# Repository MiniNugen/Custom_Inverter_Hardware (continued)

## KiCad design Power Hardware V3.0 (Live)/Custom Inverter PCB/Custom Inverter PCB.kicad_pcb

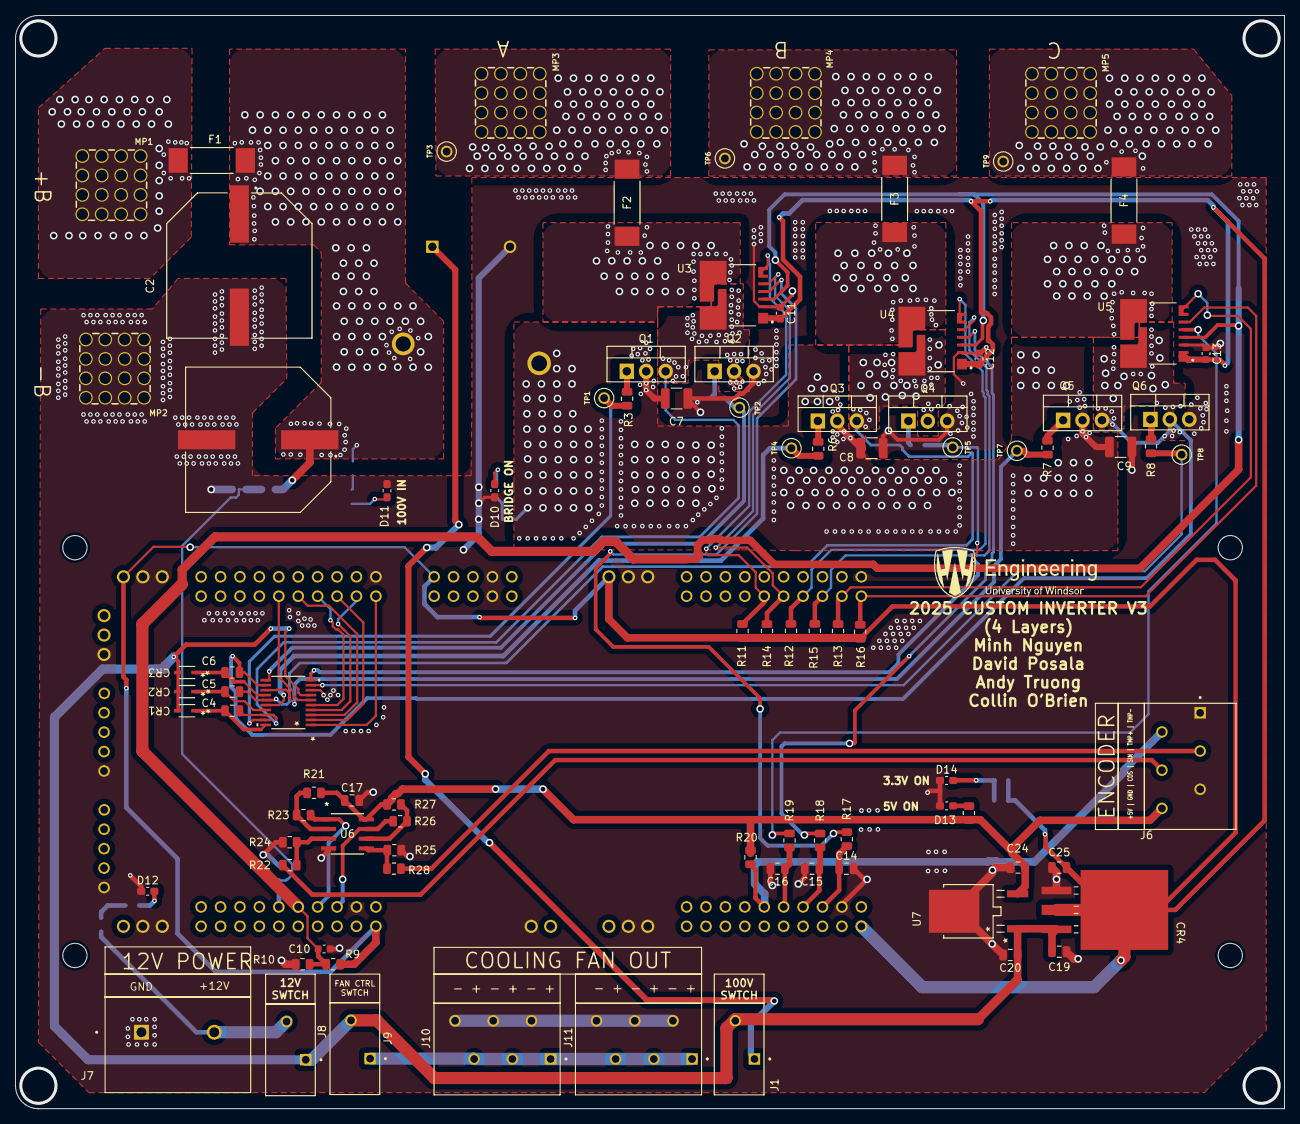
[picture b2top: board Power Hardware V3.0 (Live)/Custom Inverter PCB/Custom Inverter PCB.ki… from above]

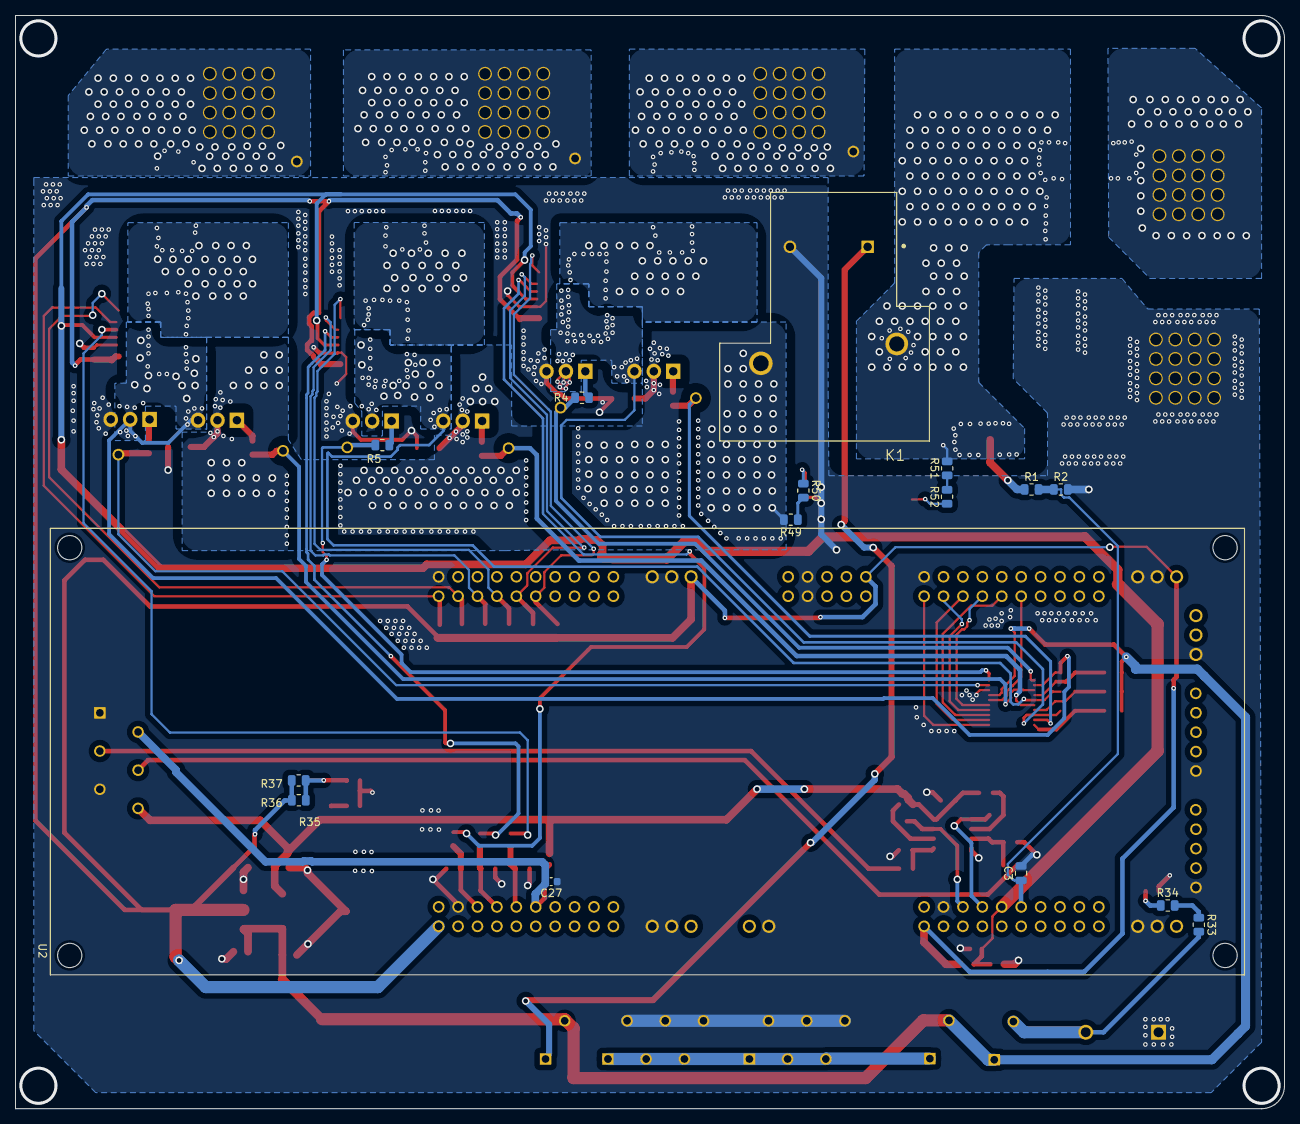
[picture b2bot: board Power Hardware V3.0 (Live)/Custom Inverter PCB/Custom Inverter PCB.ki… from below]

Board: 4 copper layers, 166.0 x 143.0 mm, 107 parts (16 on the bottom side), 71 nets.

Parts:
C1, C2: 330 µF; CAP_EEVFK2A331M
C3, C17, C24, C25: 0.1uF; C_0805_2012Metric
C4, C5, C6: 1uF; C_0805_2012Metric
C7, C8, C9: 1uF; C_1210_3225Metric
C10, C11, C12, C13, C27: 220nF; C_0603_1608Metric
C14, C15, C16: 47nF; C_0805_2012Metric
C19, C20: 0.33uF; C_0805_2012Metric
CR1, CR2, CR3: CR_SOD-323_MCC
CR4: LD1085D2M33R; D2PAK&slash_A_STM
D10: BRIDGE ON; C_0603_1608Metric_Pad1.08x0.95mm_HandSolder
D11: 100V IN; C_0603_1608Metric_Pad1.08x0.95mm_HandSolder
D12: 12V; C_0603_1608Metric_Pad1.08x0.95mm_HandSolder
D13: 5V; C_0603_1608Metric_Pad1.08x0.95mm_HandSolder
D14: 3.3V; C_0603_1608Metric_Pad1.08x0.95mm_HandSolder
F1: 100VDC 50A; FUSE_0463_LTF-M
F2, F3, F4: 250VAC 50A; FUSE_0463_LTF-M
J1, J8, J9: 1990009; PHOENIX_1990009
J6, J10, J11: 1990041; PHOENIX_1990041
J7: 1714971; PHOENIX_1714971
K1: 1-1393210-3; TE_1-1393210-3
MP1, MP2, MP3, MP4, MP5: 7461383; WP-SHFU_7461383
Q1, Q2, Q3, Q4, Q5, Q6: IRFB4115PBF; TO-220-3_Vertical
R1: 97.6K; R_0805_2012Metric
R2, R22, R23, R26, R28: 3K; R_0805_2012Metric
R3, R4, R5, R6, R7, R8: 15R; R_0805_2012Metric
R9, R10, R11, R12, R13, R14, R15, R16: 4.7K; R_0805_2012Metric
R17, R18, R19, R33, R34, R35, R36, R37: 220R; R_0805_2012Metric
R20: 5.36k; R_0805_2012Metric
R21, R24, R25, R27: 10k; R_0805_2012Metric
R49, R50, R51, R52: 2.7k; R_0805_2012Metric
TP1, TP2, TP3, TP4, TP5, TP6, TP7, TP8, TP9: 5002; KEYSTONE_5002
U1: DRV8300DIPWR; TSSOP_0DIPWR_TEX
U2: LAUNCHXL-F280049C; MODULE_LAUNCHXL-F280049C
U3, U4, U5: TLI4971A050T5E0001XUMA1; TLI4971A050T5UE0001XUMA1
U6: OP292GSZ-REEL; R_8_ADI
U7: L78M05CDT-TR; DPAK_STM-M

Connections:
+3.3VDC: C11.2, C12.2, C13.2, C25.1, CR4.2 (OUTPUT), CR4.4 (OUTPUT), R9.1, R11.1, R12.1, R13.1, R14.1, R15.1, R16.1, R36.2, R37.2, U2.J1_1 (+3.3V), U2.J5_41 (J5_+3.3V), U2.J11_10 (+3.3V), U2.JP4_1 (+3.3V), U2.JP6_1 (+3.3V), U3.1 (VDD), U4.1 (VDD), U5.1 (VDD)
+5V: C17.1, C24.1, J6.6, R20.2, R21.1, R27.1, R35.2, U6.8 (+V), U7.2 (OUTPUT)
+12V to relay: J7.2, J8.2, R33.2
+12VDC: C19.1, C20.1, CR1.2, CR2.2, CR3.2, CR4.3 (INPUT), J1.2, J8.1, J9.2, U1.7 (GVDD), U7.1 (INPUT)
+100VDC: C7.1, C8.1, C9.1, K1.NO, Q1.2 (D), Q3.2 (D), Q5.2 (D), R49.2
+100VDC to Relay: C1.1, C2.1, F1.2, K1.C, R1.1, R51.2
/Current sense/1_Out: R17.1, U3.4 (AOUT)
/Current sense/2_Out: R18.1, U4.4 (AOUT)
/Current sense/3_Out: R19.1, U5.4 (AOUT)
/Current sense/IA-: F2.1, U3.7 (IP-)
/Current sense/IB-: F3.1, U4.7 (IP-)
/Current sense/IC-: F4.1, U5.7 (IP-)
/Current sense/ISENA: C14.1, R17.2, U2.J3_23 (ADCINA5)
/Current sense/ISENB: C15.1, R18.2, U2.J3_24 (ADCINB0)
/Current sense/ISENC: C16.1, R19.2, U2.J3_25 (ADCINC2)
/Current sense/OCD1_A: R14.2, U2.J4_36 (GPIO4), U3.5 (OCD1)
/Current sense/OCD1_B: R15.2, U2.J4_38 (GPIO8), U4.5 (OCD1)
/Current sense/OCD1_C: R16.2, U2.J4_40 (GPIO10), U5.5 (OCD1)
/Current sense/OCD2_A: R11.2, U2.J4_35 (GPIO5), U3.6 (OCD2)
/Current sense/OCD2_B: R12.2, U2.J4_37 (GPIO9), U4.6 (OCD2)
/Current sense/OCD2_C: R13.2, U2.J4_39 (GPIO11), U5.6 (OCD2)
/Current sense/Vref: C10.1, R9.2, R10.1, U2.J7_65 (ADCINC14), U3.3 (VREF), U4.3 (VREF), U5.3 (VREF)
/Encoder Input/COS_IN: J6.4, R22.1
/Encoder Input/COS_MCU: R23.1, U2.J7_64 (ADCINA2), U6.1 (OUTA)
/Encoder Input/SIN_IN: J6.3, R28.2
/Encoder Input/SIN_MCU: R26.1, U2.J7_63 (ADCINA6), U6.7 (OUTB)
/Encoder Input/Temp+: C27.1, J6.2, R20.1, U2.J3_26 (ADCINB1)
/GateDriver&Power Inputs/CBSTA_HI: C4.1, CR1.1, U1.20 (BSTA)
/GateDriver&Power Inputs/CBSTB_HI: C5.1, CR2.1, U1.17 (BSTB)
/GateDriver&Power Inputs/CBSTC_HI: C6.1, CR3.1, U1.14 (BSTC)
/GateDriver&Power Inputs/GHA: R3.1, TP1.TP, U1.19 (GHA)
/GateDriver&Power Inputs/GHB: R6.1, TP4.TP, U1.16 (GHB)
/GateDriver&Power Inputs/GHC: R7.1, TP7.TP, U1.13 (GHC)
/GateDriver&Power Inputs/GLA: R4.1, TP2.TP, U1.11 (GLA)
/GateDriver&Power Inputs/GLB: R5.1, TP5.TP, U1.10 (GLB)
/GateDriver&Power Inputs/GLC: R8.1, TP8.TP, U1.9 (GLC)
/GateDriver&Power Inputs/PVDD: F1.1, MP1.1, MP1.2, MP1.3, MP1.4, MP1.5, MP1.6, MP1.7, MP1.8, MP1.9, MP1.10, MP1.11, MP1.12, MP1.13, MP1.14, MP1.15, MP1.16
/INHA: U1.1 (INHA), U2.J8_80 (GPIO0)
/INHB: U1.2 (INHB), U2.J8_78 (GPIO6_BP)
/INHC: U1.3 (INHC), U2.J8_76 (GPIO2_BP)
/INLA: U1.4 (INLA), U2.J8_79 (GPIO1)
/INLB: U1.5 (INLB), U2.J8_77 (GPIO7_BP)
/INLC: U1.6 (INLC), U2.J8_75 (GPIO3)
/MOTA: F2.2, MP3.1, MP3.2, MP3.3, MP3.4, MP3.5, MP3.6, MP3.7, MP3.8, MP3.9, MP3.10, MP3.11, MP3.12, MP3.13, MP3.14, MP3.15, MP3.16, TP3.TP
/MOTB: F3.2, MP4.1, MP4.2, MP4.3, MP4.4, MP4.5, MP4.6, MP4.7, MP4.8, MP4.9, MP4.10, MP4.11, MP4.12, MP4.13, MP4.14, MP4.15, MP4.16, TP6.TP
/MOTC: F4.2, MP5.1, MP5.2, MP5.3, MP5.4, MP5.5, MP5.6, MP5.7, MP5.8, MP5.9, MP5.10, MP5.11, MP5.12, MP5.13, MP5.14, MP5.15, MP5.16, TP9.TP
/SEN_100V: C3.1, R1.2, R2.1, U2.J7_66 (ADCINC1)
/SHA: C4.2, Q1.3 (S), Q2.2 (D), U1.18 (SHA), U3.8 (IP+)
/SHB: C5.2, Q3.3 (S), Q4.2 (D), U1.15 (SHB), U4.8 (IP+)
/SHC: C6.2, Q5.3 (S), Q6.2 (D), U1.12 (SHC), U5.8 (IP+)
Fan_Power: J9.1, J10.1, J10.3, J10.5, J11.1, J11.3, J11.5
GND: C1.2, C2.2, C3.2, C7.2, C8.2, C9.2, C10.2, C11.1, C12.1, C13.1, C14.2, C15.2, C16.2, C17.2, C19.2, C20.2, C24.2, C25.2, C27.2, CR4.1 (ADJ/GND), D10.1 (K), D11.1 (K), D12.1 (K), D13.1 (K), D14.1 (K), J6.1, J6.5, J7.1, J10.2, J10.4, J10.6, J11.2, J11.4, J11.6, K1.A2, MP2.1, MP2.2, MP2.3, MP2.4, MP2.5, MP2.6, MP2.7, MP2.8, MP2.9, MP2.10, MP2.11, MP2.12, MP2.13, MP2.14, MP2.15, MP2.16, Q2.3 (S), Q4.3 (S), Q6.3 (S), R2.2, R10.2, R24.2, R25.2, U1.8 (GND), U2.J2_20 (GND_1), U2.J3_22 (GND_1), U2.J6_60 (GND_1), U2.J7_62 (GND_1), U2.J11_3 (GND_1), U2.J11_4 (GND_1), U2.J12_5 (GND_1), U2.J13_5 (GND_1), U2.J14_3 (GND_1), U2.J15_2 (GND_2), U2.JP4_2 (GND_2), U2.JP4_3 (GND_2), U2.JP5_2 (GND_2), U2.JP5_3 (GND_2), U2.JP6_2 (GND_2), U2.JP6_3 (GND_2), U2.JP7_2 (GND_2), U2.JP7_3 (GND_2), U3.2 (GND), U4.2 (GND), U5.2 (GND), U6.4 (-V), U7.3 (GROUND)
unnamed: D10.2 (A), R50.1
unnamed: D11.2 (A), R52.1
unnamed: D12.2 (A), R34.1
unnamed: D13.2 (A), R35.1
unnamed: D14.2 (A), R36.1, R37.1
unnamed: J1.1, K1.A1
unnamed: Q1.1 (G), R3.2
unnamed: Q2.1 (G), R4.2
unnamed: Q3.1 (G), R6.2
unnamed: Q4.1 (G), R5.2
unnamed: Q5.1 (G), R7.2
unnamed: Q6.1 (G), R8.2
unnamed: R33.1, R34.2
unnamed: R49.1, R50.2
unnamed: R51.1, R52.2
unnamed: R22.2, R24.1, U6.3 (+INA)
unnamed: R25.1, R28.1, U6.5 (+INB)
unnamed: R21.2, R23.2, U6.2 (-INA)
unnamed: R26.2, R27.2, U6.6 (-INB)

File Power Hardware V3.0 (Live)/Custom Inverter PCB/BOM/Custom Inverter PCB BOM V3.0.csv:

"Reference","Value","Datasheet","Footprint","Qty","DNP","Part Number"
"C1,C2","330 µF","https://industrial.panasonic.com/cdbs/www-data/pdf/RDE0000/A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","EEV_FK2A331M:CAP_EEVFK2A331M","2","","EEVFK2A331M"
"C3","0.1uF","https://www.digikey.ca/en/products/detail/yageo/CC0805KRX7R9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","Capacitor_SMD:C_0805_2012Metric","1","","CC0805KRX7R9BB104"
"C4,C5,C6","1uF","https://www.digikey.ca/en/products/detail/samsung-electro-me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","Capacitor_SMD:C_0805_2012Metric","3","","CL21B105KBFNFNE"
"C7,C8,C9","1uF","https://www.digikey.ca/en/products/detail/tdk-corporation/CG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","Capacitor_SMD:C_1210_3225Metric","3","","CGA6M2X7R2A105K200AA"
"C10,C11,C12,C13,C27","220nF","~","Capacitor_SMD:C_0603_1608Metric","5","","CL21B224KAFNNNE"
"C14,C15,C16","47nF","","Capacitor_SMD:C_0805_2012Metric","3","","C0805C473K5RACTU"
"C17,C24,C25","0.1uF","https://www.digikey.ca/en/products/detail/kyocera-avx/0805ZD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","Capacitor_SMD:C_0805_2012Metric","3","","0805ZD104KAT2A"
"C19,C20","0.33uF","https://www.digikey.ca/en/products/detail/murata-electronics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","Capacitor_SMD:C_0805_2012Metric","2","","GRM219R71H334KA88D"
"CR1,CR2,CR3","~","BAV20WS-TP","BAV20WS-TP:CR_SOD-323_MCC","3","","BAV20WS-TP"
"CR4","LD1085D2M33R","https://www.st.com/content/ccc/resource/technical/document/d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","LD1085D2M33R:D2PAK&slash_A_STM","1","","LD1085D2M33R"
"D10,D11,D12,D13,D14","100V IN,12V,3.3V,5V,BRIDGE ON","https://mm.digikey.com/Volume0/opasdata/d220001/medias/docus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","Capacitor_SMD:C_0603_1608Metric_Pad1.08x0.95mm_HandSolder","5","","B1931UY--20D000114U1930"
"F1,F2,F3,F4","100VDC 50A,250VAC 50A","https://www.bourns.com/docs/Product-Datasheets/SF-3812F-T.pdf","0463030_ER:FUSE_0463_LTF-M","4","","SF-3812F5000T-2"
"J1,J8,J9","1990009","","2P term 1990009:PHOENIX_1990009","3","","1990009"
"J2,J3,J4,J5","10897202","10897202","CONN20_0010897202_MOL","4","","10897202"
"J6,J10,J11","1990041","","PHOENIX_1990041:PHOENIX_1990041","3","","1990041"
"J7","1714971","","1714971:PHOENIX_1714971","1","","1714971"
"K1","1-1393210-3","https://www.te.com/en/product-1-1393210-3.datasheet.pdf","T9AS1D12_12:TE_1-1393210-3","1","","1-1393210-3"
"MP1,MP2,MP3,MP4,MP5","7461383","7461383","M5 Screw Term 7461383:WP-SHFU_7461383","5","","7461383"
"Q1,Q2,Q3,Q4,Q5,Q6","IRFB4115PBF","https://www.infineon.com/dgdl/irfb4115pbf.pdf?fileId=5546d46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","Package_TO_SOT_THT:TO-220-3_Vertical","6","","IRFB4115PBF"
"R1","97.6K","https://www.digikey.ca/en/products/detail/yageo/RC0805FR-079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","Resistor_SMD:R_0805_2012Metric","1","","RC0805FR-0797K6L"
"R2,R22,R23,R26,R28","3K","https://www.digikey.ca/en/products/detail/te-connectivity-pa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","Resistor_SMD:R_0805_2012Metric","5","","CRG0805F3K0"
"R3,R4,R5,R6,R7,R8","15R","https://www.digikey.ca/en/products/detail/panasonic-electron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","Resistor_SMD:R_0805_2012Metric","6","","ERJ-6GEYJ150V"
"R9,R10,R11,R12,R13,R14,R15,R16","4.7K","~","Resistor_SMD:R_0805_2012Metric","8","","CRCW08054K70FKEAC"
"R17,R18,R19,R33,R34,R35,R36,R37","220R","CRGCQ0805F220R","Resistor_SMD:R_0805_2012Metric","8","","CRGCQ0805F220R"
"R20","5.36k","https://www.yageo.com/upload/media/product/products/datashee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","Resistor_SMD:R_0805_2012Metric","1","","RC0805FR-075K36L"
"R21,R24,R25,R27","10k","https://industrial.panasonic.com/cdbs/www-data/pdf/RDM0000/A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","Resistor_SMD:R_0805_2012Metric","4","","ERA-6AEB103V"
"R49,R50,R51,R52","2.7k","https://industrial.panasonic.com/cdbs/www-data/pdf/RDO0000/A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","Resistor_SMD:R_0805_2012Metric","4","","ERJ-P06J272V"
"TP1,TP2,TP3,TP4,TP5,TP6,TP7,TP8,TP9","5002","","5002:KEYSTONE_5002","9","","5002"
"U1","DRV8300DIPWR","https://www.ti.com/lit/ds/symlink/drv8300.pdf","DRV8300DIPWR:TSSOP_0DIPWR_TEX","1","","DRV8300DIPWR"
"U2","LAUNCHXL-F280049C","https://www.ti.com/lit/ug/spruii7b/spruii7b.pdf?ts=1748422871760","LAUNCHXL-F280049C:MODULE_LAUNCHXL-F280049C","1","","LAUNCHXL-F280049C"
"U3,U4,U5","TLI4971A050T5E0001XUMA1","https://www.infineon.com/dgdl/Infineon-TLI4971_25_50_75_120-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","TLI4971A:TLI4971A050T5UE0001XUMA1","3","","TLI4971A050T5E0001XUMA1"
"U6","OP292GSZ-REEL","https://www.analog.com/media/en/technical-documentation/data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","R_8_ADI","1","","OP292GSZ-REEL"
"U7","L78M05CDT-TR","L78M05CDT-TR","L78M05CDT_TR:DPAK_STM-M","1","","L78M05CDT-TR"

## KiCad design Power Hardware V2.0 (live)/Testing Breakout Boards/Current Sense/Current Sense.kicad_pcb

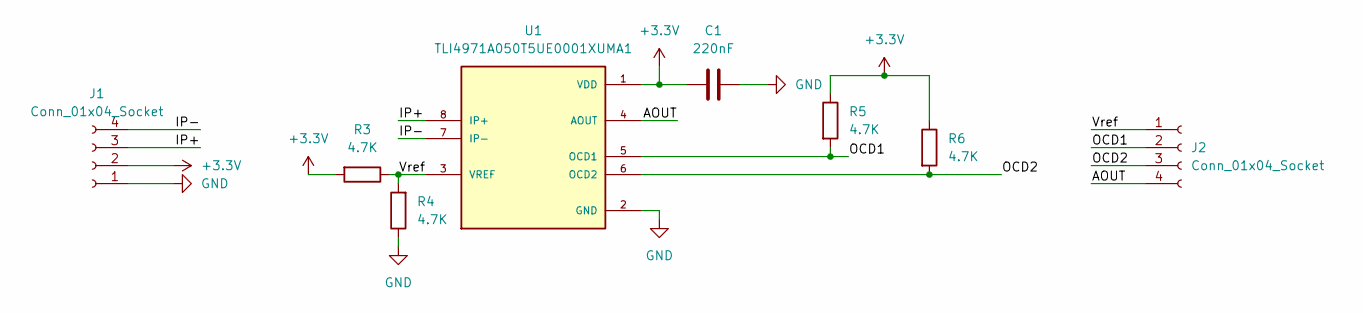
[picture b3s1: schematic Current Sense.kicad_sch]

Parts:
C1: 220nF; C_0603_1608Metric; Part Number CL21B224KAFNNNE
J1, J2: Conn_01x04_Socket; PinHeader_1x04_P2.54mm_Vertical; Part Number RS1-04-G
R3, R4, R5, R6: 4.7K; R_0805_2012Metric; Part Number CRCW08054K70FKEAC
U1: TLI4971A050T5UE0001XUMA1; PARTREV 1.20

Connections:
+3.3V: C1.1, J1.2, R3.2, R5.1, R6.1, U1.1 (VDD)
/AOUT: J2.4, U1.4 (AOUT)
/IP+: J1.3, U1.8 (IP+)
/IP-: J1.4, U1.7 (IP-)
/OCD1: J2.2, R5.2, U1.5 (OCD1)
/OCD2: J2.3, R6.2, U1.6 (OCD2)
/Vref: J2.1, R3.1, R4.2, U1.3 (VREF)
GND: C1.2, J1.1, R4.1, U1.2 (GND)

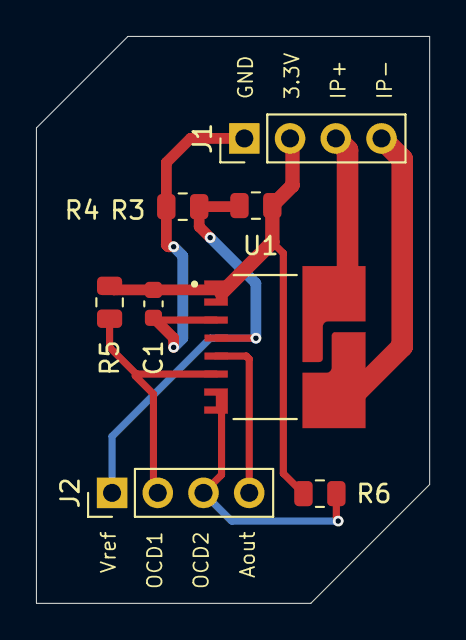
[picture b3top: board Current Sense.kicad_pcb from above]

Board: 2 copper layers, 21.8 x 31.5 mm, 8 parts (0 on the bottom side), 8 nets.

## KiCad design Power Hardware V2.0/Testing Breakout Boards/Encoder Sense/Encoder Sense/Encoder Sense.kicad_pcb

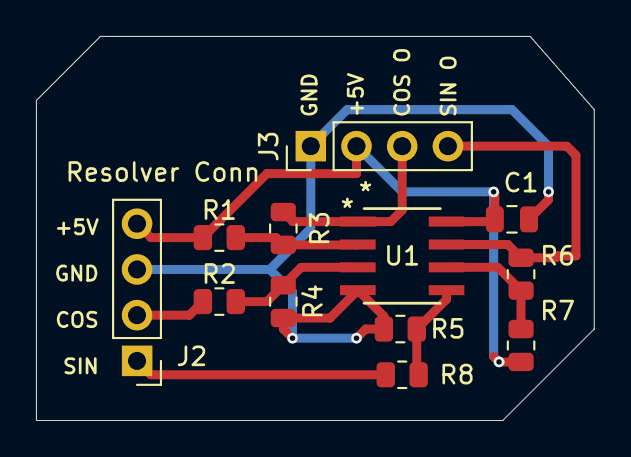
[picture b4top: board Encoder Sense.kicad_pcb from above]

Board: 2 copper layers, 31.0 x 21.3 mm, 12 parts (0 on the bottom side), 10 nets.

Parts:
C1: 0.1uF; C_0805_2012Metric
J2, J3: Conn_01x04_Socket; PinHeader_1x04_P2.54mm_Vertical
R1, R4, R5, R7: 10k; R_0805_2012Metric
R2, R3, R6, R8: 3K; R_0805_2012Metric
U1: OP292GSZ-REEL; R_8_ADI

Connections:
+5V: C1.1, J2.4, J3.2, R1.1, R7.1, U1.8 (+V)
/COS_IN: J2.2, R2.1
/COS_MCU: J3.3, R3.1, U1.1 (OUTA)
/SIN_IN: J2.1, R8.2
/SIN_MCU: J3.4, R6.1, U1.7 (OUTB)
GND: C1.2, J2.3, J3.1, R4.2, R5.2, U1.4 (-V)
unnamed: R2.2, R4.1, U1.3 (+INA)
unnamed: R5.1, R8.1, U1.5 (+INB)
unnamed: R1.2, R3.2, U1.2 (-INA)
unnamed: R6.2, R7.2, U1.6 (-INB)

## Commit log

2024-12-09 Revision 1 of control board
2025-02-28 Added Live version of Power hardware KiCAD
2025-03-15 switches instead of relays. Short on half bridge fixed. encoder page made. root page connections fixed
2025-03-18 Schematic Changes
    -Changed 3.3V regulator to a higher power unit for the sin-cos circuit (from 500mA to 3A)
    -Fixed flipped MOTA,B,C connection to Output Terminal
    - Current Sense IC setup
    - Fuses for Phase current outputs
2025-03-28 Updated parts numbers for current sensing
2025-03-29 no changes
    no
2025-04-13 no major changes
2025-04-19 Sine-cos test
2025-04-20 Resolver Reading opamps
2025-04-20 EDA models
    EDA models
2025-04-20 footprint lib fixes
2025-04-20 footprint fixes
2025-04-20 model fixes
2025-04-21 Pcb layout and tracing
    changed footprint file for current sense ic
    did layout and tracing for pcb
    created bom
2025-04-22 PCB Fixes
2025-04-22 GERBERS
2025-04-22 Fixed con issue with trace interfering with mosftet HVDC connection
2025-05-02 breakout boards
2025-05-27 Ver2.1 pushed
    Error fixes:
    -floating plane
    - Unconnected sinecose node
    - Standoff rubbing
2025-05-28 Datasheets into components
2025-06-22 Added 100-12 and 12-5 regulators added fan headers
2025-06-26 Fixes
2025-06-27 PCB V3 changes
    -HV outputs and inputs changed to screw terminals for lugs
    - Fuses changes to 50A
    - ADC pin for temp sense along with the temp sensing circuit
    - Added more pins to motor encoder term for temp sense
2025-06-27 PCB layout
2025-06-28 V3 layout
2025-06-28 layout
2025-06-28 V3.0 is ordered
2025-06-30 V3 push
2025-06-30 3D models added
    Added most of the 3D models will add more to complete
2025-07-02 BOM list
2025-07-15 3d models
